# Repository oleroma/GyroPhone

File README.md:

<h1 align="center">
  <picture>
    <source media="(prefers-color-scheme: dark)" srcset="./media/logo_light.svg">
    <source media="(prefers-color-scheme: light)" srcset="./media/logo_dark.svg">
    <!-- The fallback image for older browsers -->
    
  </picture>
  <br>
</h1>

# GyroPhone

GyroPhone turns an Android phone into a game pad, keyboard, mouse and gyro aim for a Windows PC, in the spirit of the [Alpakka](https://github.com/inputlabs/alpakka_firmware) controller. The phone's gyro aims like a mouse. The touchscreen is a laptop-style touchpad plus any buttons and sticks you place on it. A controller, keyboard or mouse attached to the phone can be remapped too. Everything is a mapping you can change: any input can press any output.

It connects two ways:

- **Bluetooth**: the phone is a Bluetooth game pad, keyboard and mouse. Nothing is installed on the PC. Windows sees a DirectInput pad, and input is limited to 30–90 reports a second.
- **Wi-Fi or USB, with the companion**: a small Windows tray app (`GyroPhoneCompanion.exe`) receives up to 1000 updates a second, encrypted. It gives games a virtual **Xbox 360** or **DualShock 4** pad and real keyboard and mouse input, and can draw the phone's motion as overlay windows over the game or for OBS. This is the low-latency way to play.

The reference phone is a OnePlus 15 (Android 16, no root). Android 15 or newer is needed.

The full description of every feature and how it works inside is in the **[spec](docs/spec/README.md)**.

## Setting up

### Phone

Install the APK (`gyrophone-0.1.<build>.apk`). Builds are published as pre-releases on this repo, so [Obtainium](https://github.com/ImranR98/Obtainium) can install and update it (add the repo with pre-releases on). Open GyroPhone and allow the nearby-devices (Bluetooth) and notification permissions. The app opens on the pad.

### Bluetooth (no PC install)

1. On the pad, tap **Connection**, choose **Bluetooth**, and tap **Make discoverable**.
2. On Windows: Settings › Bluetooth & devices › Add device, and pick **GyroPhone**.
3. The phone reconnects to that PC by itself from then on. Set **Report rate** on the same page (60 Hz by default; higher rates queue up and lag on phones that force Bluetooth sniff mode).

### Wi-Fi and USB (companion)

On the PC:

1. Get `GyroPhoneCompanion.exe` from the same pre-release (Windows 10/11 x64), put it in `%LOCALAPPDATA%\Programs\GyroPhone\`, and run it. It is unsigned, so SmartScreen may ask: *More info* › *Run anyway*.
2. For the game pad, install the **ViGEmBus** driver ([github.com/nefarius/ViGEmBus/releases](https://github.com/nefarius/ViGEmBus/releases)). Without it keyboard and mouse still work, and Home in the companion shows how to fix it.
   - Optional: for a **DualSense** pad, run `install.cmd` from the unpacked driver package (`build\GyroPhonePad-driver` after a PC build, or the `GyroPhonePad-driver.zip` of a release), then restart the companion. It's our own user-mode driver, signed with a key made for your PC only; `uninstall.cmd` removes it. Buttons and sticks only for now. See [driver/README.md](driver/README.md).
3. Allow it through the firewall on **Private** networks. The companion never opens Public networks, so if the phone can't connect, set your home Wi-Fi to Private (Home says so when the network is Public and no phone is seen). The Connection page has fix buttons for the firewall and USB rules.
4. On the first run the **Pair new phone** window opens by itself. Later, use *Pair new phone…* in the tray menu.

On the phone:

1. Tap **Connection**, choose **Wi-Fi**, tap **Scan QR code**, and point the camera at the QR code in the PC's pairing window. That's all: both sides trust each other's key, and the phone connects by itself whenever GyroPhone is open (**Connect automatically**, on by default).
2. Or pair with a code: tap the PC under *Found on this network* (or type its address under *Enter PC address*). Check the six-digit code matches on both screens, then tap **Confirm** on the phone and **Allow** on the PC.
3. Keep GyroPhone on screen while playing: Android only grants the low-latency Wi-Fi mode to the app in front. **Link quality** shows the rate, loss and latency.

**USB.** With USB tethering on, the link moves to the cable by itself. With the phone's USB mode set to *No data transfer*, the companion can also use the cable directly (Android asks to open GyroPhone for the accessory; say yes).

**Starting automatically.** In the companion's App page: **Start with Windows**, or **Start when my phone appears** (a tiny watcher starts the companion when the phone looks for this PC).

## The pad

The app is the pad. Along the top is the **capsule row**:

- **+** adds a workspace (Controller, WASD, Keyboard or a blank one, with the touchpad only);
- one capsule per **workspace**: tap to switch, **tap the current one to edit it**;
- **Controller**: what attached devices do;
- **Settings** and **Connection**.

Long-press a capsule and drag it to reorder. The **← / →** corners switch to the previous / next workspace. Press **both together for fullscreen**; press them again, or Back, to leave.

Empty space is the **touchpad**. With the Windows touchpad preset (in the three starting workspaces): one finger moves the cursor, tap clicks, tap-and-drag drags, two fingers scroll, two-finger tap right-clicks, pinch zooms, and three- and four-finger swipes and taps do Task View, show desktop, switch apps, switch desktops and the notification centre. If your phone takes three-finger touches for screenshots, turn that gesture off in the phone's settings.

### Workspaces

A **workspace** is one complete setup: its buttons, sticks and touchpad, their mappings, its gyro and touch settings, its layers, and which **device preset** it uses for attached devices. Workspaces share nothing, so you can duplicate one and change it freely. There are no game profiles and no automatic switching: switch with the capsules or corners.

Settings and mappings pass down: **Defaults** (Settings › Defaults) → **workspace** → **layer** → **button**. A level only stores what it changes. Values a level sets itself are highlighted, and **↺** makes one follow its parent again.

### Edit mode

Tap the current workspace's capsule. A floating menu appears. Drag it by its ⠿ dots to reach what's under it, and drag its right edge to make it wider or narrower. Everything except undo and redo scrolls sideways, so swipe the menu's rows to reach the rest on a narrow (portrait) screen.

- **Tap** a control to select it. Tapping again where controls overlap selects the next one underneath, so taps cycle through a stack.
- **Drag** moves the selected control *from anywhere on the screen*, not only from on top of it, so small controls don't hide under your finger. With nothing selected, a drag moves the control under the finger.
- **Pinch** with two fingers anywhere resizes the selected control. On a rectangle, the pinch locks to one axis if your fingers spread mostly one way (width or height only), and frees the other axis once that one changes too. A **two-finger tap** selects the control under the fingers without opening anything.
- **Long-press** (about half a second) a control to open its mapping editor. Long-press **empty space** for the workspace touchpad's mapping editor. Long-press a **← / → corner** for its size and "Same size for all corners", or a **gyro display** for its settings.
- **Tap empty space** to clear the selection.
- **+ Button**, **+ Empty button** (one that inherits nothing from the touchpad), **+ Stick**, and the **gyro displays** (3D phone, Ratchet ring, Speed graph, Attitude indicator, Bubble disk, 3D shape). Tapping one adds it in the middle; **dragging it out of the menu** drops it where you let go.
- **Configure** opens the selected control's settings; **Map** opens its mapping editor.
- **Select** turns taps into multi-pick (a picked control's whole group comes with it), and a drag then moves everything picked. **Group** / **Ungroup** keep controls together for later moves and pinches. **Snap** puts edges on a grid. 🔒 **Lock layout** stops drags and pinches from moving what was already there; controls you add afterwards stay free until edit mode opens again.
- **Devices** picks the workspace's device preset. **Library** adds a button you saved earlier ("Save to library" in a button's settings); long-press a library button to remove it from the library.
- **↶ / ↷** undo and redo (100 steps; a slider drag counts as one step). **⚙** saves your edits so far and opens the workspace's settings; Back returns to edit mode. **Done** saves; **Cancel** asks before throwing changes away. Your edits survive the app being sent to the background.

Landscape and portrait have separate placements, so edit in the orientation you play in.

## The mapping editor

Every button, stick, the touchpad, the Defaults, and every key of an attached device have the same full-screen mapping editor.

**Layout.** The top half lists the control's **actions** as cards: one per input (for a button: its press, then its touch gestures). Each card holds the outputs it presses as **chips**. The bottom half is the **library** of outputs in tabs: Recent, Presets, Keyboard, Mouse, Gamepad, Gyro, Phone, Touchpad, Layers, Other. A search box finds any output ("W", "LT", "wheel"), and **⌨ Press a key** captures a key from an attached keyboard. Drag the divider to give either half more room.

**Mapping something:**

1. Tap a card to select it, then tap an output in the library to add it there. Tap several outputs to add them all.
2. Or long-press an output and drag it onto any card.
3. Long-press a chip to drag it to another card, or back onto the library to remove it. While dragging, hold near the top or bottom edge to scroll the cards.
4. Reorder cards by their ⠿ handle. **Sort ▾** puts them back in the default order, your own (Custom), or Mapped first.
5. Adding an output a card already presses moves it to the next free **When** and opens its settings, so dropping "Crouch" twice gives you On touch Crouch and Long press Crouch.

**Finger chips** (on buttons and the touchpad) pick which finger count you are mapping: **1–4 fingers**, each with its own taps, holds, swipes, Move X / Move Y and pinch. **Motion** maps the gyro, tilt and shake (on a button: what they do while it is held).

Under a card, a grey line shows its timings ("Tap: at lift before 400 ms · Long press: from 400 ms"). A card's **⚙** opens that input's own settings, such as its own long-press time or a swipe direction's distance and pie.

**Chip settings.** Tap a chip to open its settings:

- **Where** (touch controls): **Touch** (the press), **Inside** (any finger inside the control, wherever it touched down), **Outside** (a finger that touched down on it and slid off).
- **When**: **On touch** (held from touch-down to lift), **Tap**, **Long press**, **Double tap**, **Release**. On swipe directions these read On swipe, Quick swipe, Long hold, Double swipe. Each When is a separate input, so one button can do different things on tap, long press and double tap. A tap only waits for a possible double tap when the double tap does something else.
- **How**: **Held** (for as long as it lasts), **Once** (one short press), **Toggle** (on, then off next time). A Toggle can **also end on** a tap, Let go, a timer, the next input (a sticky Shift), or the same keystroke.
- **Advanced**: start delay, end delay, hold at least, and **Cycle** (the outputs take turns, one per press).
- Analog outputs (mouse motion, sticks) have a **scale**; −1 inverts.

**Inherited mappings** show faded. **✕** clears one (the input then does nothing here), **↺** follows the parent again, **↺ Reset all** follows everything, and **✕ Clear all** clears everything. **↶ Undo** undoes any change.

**Swipe length zones.** A held swipe direction (Swipe ← → ↑ ↓) can do different things the further you swipe. Its row ends in a divider: drag a chip **past that end divider** to make a new zone. Long-press a divider to slide it, and tap the end divider for the last zone's settings (its length and Keep: Only in zone, Only forward, Always). A held direction **latches** (stays on after you lift) when one of its chips is a Toggle that also ends on Tap.

**Layers.** Chips at the top pick **Base** or a layer (**+ Layer**, up to 9). Long-press a layer chip to rename or delete it. A mapping in a layer only works while that layer is in use. Map an input to a **Layer** output (Layers tab) to **switch** to it, **override** Base with it (inputs the layer doesn't map keep their Base mapping), or use it only **while held**. **Layer back** returns to the previous layer. A layer can also have its own settings, for example a lower gyro sensitivity.

**Presets** fill in common setups: **Windows touchpad** for a touch surface, **Gyro mouse** for the gyro (yaw → Move X, pitch → Move Y), and Left stick, Right stick, WASD, Arrow keys and D-pad for sticks.

**⚙ Settings** opens the control's own settings: label, shape and size, layer behaviour, its own touch surface settings, a stick's deadzone and zones, and its own gyro sensitivity while held (for precision aim). For a button it also has **Duplicate**, **Save to library** and **Delete**.

## Gyro aiming

The gyro is mapped like everything else: in the Motion tab, map **yaw / pitch / roll** to mouse Move X / Y, scroll, or a stick axis (or use the Gyro mouse preset). The three starting workspaces already have it.

**Ratchets.** Map a button to **Ratchet** (or Ratchet yaw / pitch / roll) in the Gyro tab. In the workspace's Gyro settings, **Gyro to mouse** sets what it does:

- **Ratchet enables** (default): the gyro does nothing until a ratchet is held.
- **Ratchet disables**: the gyro is always on, and holding a ratchet pauses it so you can re-centre the phone.
- **Gyro off**: the sensor isn't read at all.

**Toggle gyro** swaps the first two until you switch workspace.

**Acceleration curve editor**: tap the graph to add a point (up to 6), drag a point to move it, long-press a point to remove it. Its live line shows how fast you are turning now.

**Tuning** (workspace settings › Gyro): **Sensitivity** in mouse counts per degree (16 by default; per axis, exact, or a 0 to 1 share of the parent's with "Scale parent"); **Game**: pick the game and enter your in-game sensitivity, and the slider shows real-world sensitivity (degrees the camera turns per degree the phone turns; **Measure** helps if your game isn't listed); **Acceleration** curves; **Inertia** (keep gliding after a ratchet); **Gyro space** Local, World or Player (JoyShockMapper's player space). **Calibrate** removes drift: lay the phone still for 2 seconds. Alpakka/JoyShockMapper-style jitter cutoff and smoothing are in Settings › App › Gyro, off by default (raw gyro).

**Gyro poll rate** (Connection page, 1/2/4 kHz, default 4 kHz) is how often the app reads the sensor.

## Controllers and other devices

Attach a game pad, keyboard or mouse to the phone (USB or Bluetooth). The **Controller** capsule shows **device presets** as tabs (**+** adds one, long-press to rename, duplicate or delete). Each preset draws the device: the controller from the front and the back, the keyboard, the mouse, and the phone's volume rocker. Tap any control to open its mapping editor. Every key has the same When / How choices as touch buttons, and a **Motion** tab for what the gyro does while it is held. Stick deadzones, curve and direction pies, and trigger press and full-pull points are in each stick's and trigger's settings. A workspace uses one preset; pick it in edit mode with **Devices**.

**Volume rocker.** While the pad is open, the phone's volume keys turn the **PC's** volume unless you map them to something else (Controller › Phone).

**A controller plugged into the PC** can ratchet the phone's gyro with no extra delay: turn on **Use PC controller for gyro ratchet** (Connection page, Wi-Fi). The ratchet buttons come from the workspace's device preset, and the rest of the controller goes to the game as usual.

## Settings

- **Settings › App**: fullscreen on start, keep the screen on (on by default), **black screen when idle** (the pad goes black after a while without a touch, to save battery while you use a controller; tap to wake, and that tap presses nothing), screen rotation, **send input only while the pad is open** (on by default), corners, touch display (show touches, trails, live mappings), gyro filters, debug tools, and the gyro rate.
- **Settings › Defaults**: the settings and touchpad/motion mappings every workspace uses unless it sets its own.
- **Workspace settings** (⚙ in edit mode): rename, duplicate, delete, copy mappings from another workspace; gyro, tilt and shake, calibration, control opacity, haptics, gesture timings (long press 400 ms and double tap 300 ms by default), and the touchpad. Chips at the top switch between Base and each layer's own settings.
- **Connection**: the link, pairing, report rate, gyro poll rate, PC controller ratchet, and **Stop when idle** (the connection ends after the app has been off screen for 10 minutes by default).

Every settings page has a search box; on Settings it searches App and Defaults at once. Categories fold, and you can **long-press a category's name and drag it** to reorder. Values a workspace or layer sets itself are highlighted with a **↺** to follow the parent again. A ⚙ next to a gyro or touchpad setting opens per-axis or per-direction values.

## The companion

**Tray menu**: status, **Open GyroPhone**, **Pause input**, **Gamepad output** (Xbox 360 / DualShock 4 / DualSense, only with the pad driver / Off), **Overlays**, **Pair new phone…**, **Exit**.

**Main window**: **Home** (problems and their fixes, phone, link, latency and gamepad cards), **Phones** (paired phones, Forget), **Gamepad**, **Overlays**, **Connection** (network, firewall, USB checks), **App** (startup, tray click, logs, Debug window, version).

**Overlays.** Add any number of overlay windows: **Phone** (the phone in 3D with your layout, touches and presses, optionally with controller handles), **3D shape**, **Attitude indicator**, **Bubble disk**. Each has its own size, look, quality, frame rate and turning options (gravity, compass, ease back to straight, Level). Turn on **Edit** to drag and resize them; otherwise the mouse goes through them. For streaming, set the background to **Green** and use an OBS chroma key, with OBS Window Capture. Shortcuts: **Ctrl+Alt+R** Level all, **Ctrl+Alt+O** hide all, **Ctrl+Alt+E** Edit (changeable).

**Updates.** A new build placed next to the running exe as `GyroPhoneCompanion.exe.new` is picked up within seconds: the companion shuts down cleanly, replaces itself and starts again, and the phone reconnects. Settings and pairing in `%APPDATA%\GyroPhone` are kept.

### Things to know

- **Games running as administrator** don't accept injected keyboard and mouse input from a normal app. Home says so: use **Restart as administrator**. The virtual pad isn't affected.
- **Anti-cheat** may ignore injected keyboard and mouse input. Use the game pad output in those games.
- **DualShock 4 and DualSense output carry the phone's gyro and accelerometer**, like a real pad, so games with their own controller gyro (The Finals, Steam Input) can aim with it. It's easy to miss: it moves nothing until you turn on the game's gyro, and then turn the app's gyro mouse off in that workspace, or both move the camera. **Start the game after the phone connects**: games look for gyro only on pads present at launch. Which phone axis drives the pad's yaw, pitch and roll (and Invert) is in workspace settings › Gyro › **PC pad yaw / pitch / roll**; by default the screen is the pad's face (yaw through the screen). In Steam, turn off PlayStation controller support for the game if Steam takes over the pad.
- **Safety.** If the phone goes quiet for 250 ms, or the PC locks or sleeps, everything held is released. If the companion is killed while a key is held, it releases it on its next start.
- **Enhance pointer precision** in Windows changes how gyro moves the desktop cursor. Games that read raw input aren't affected.
- **Bluetooth smooth scrolling** needs the PC to have paired with a current build. After updating from an old one, remove GyroPhone in Windows Bluetooth settings and pair again once.

## Easy to miss

Gestures and actions with no button of their own:

**On the pad**
- **Tap the workspace you're on** (its capsule) to open edit mode. There is no Edit button.
- **Press ← and → together** for fullscreen. In fullscreen they are the only way out besides Back, which is why they never fade below 25 %.
- With **Hide the ← / → corners** on (Settings › App › Corners), **four quick taps anywhere** (or touching where a corner is) bring them back for 3 seconds.
- **Long-press a capsule and drag** to reorder workspaces, Controller, Settings and Connection.
- **On the black screen**, the first tap only wakes the pad; it presses nothing. A controller button mapped to **Black screen** (Other tab) blacks it out at once.
- A **one-finger hold on a button** is its press, but it also counts as a touchpad: with the button's swipes and Move mapped (or inherited from the touchpad), you can press it and aim by sliding in one motion.
- **Show live mappings on buttons** (Settings › App › Touch display) makes a button's label show what it just sent, which helps when learning tap / long press / double tap mappings.

**In the editors**
- See [Edit mode](#edit-mode) and [The mapping editor](#the-mapping-editor) for drag-from-anywhere, two-finger tap, pinch axis lock, long-press on empty space, drag-to-add, swipe zones and layer chips.
- **Controller screen**: long-press a preset's tab to rename it, duplicate it, delete it, or reset its keys' own timings.
- **Inherited values**: anything highlighted is set at this level; **↺** next to it goes back to the parent's value. Faded chips in the mapping editor are inherited; mapping anything on that input replaces them.
- Every confirm-free destructive action (**✕ Clear all**, removing chips) can be undone with **↶ Undo**.

**On the PC**
- **Edit** (tray › Overlays, or Ctrl+Alt+E) makes overlay windows draggable. A **click without a drag** picks a window for its settings, and clicking where windows overlap picks the next one underneath.
- **Level all** (Ctrl+Alt+R) makes the way you hold the phone now show face-on in every overlay.
- **Hide all** (Ctrl+Alt+O) hides every overlay but keeps each one's own Show switch for when you bring them back.
- **Clicking the tray icon** can open the main window or the pairing window: App › Tray icon.
- **Recording on the phone** (debug panel › Record) also saves the PC's side at the same moment.

## Debugging

- **Phone**: Settings › App › Debugging › **Debug tools** shows a panel on the pad with the link, gyro, workspace and layer, what is held, and the newest events. **Record** saves the last 30 s. With the switch off nothing is logged.
- **PC**: App page › **Debug window…** shows the link as the PC sees it, what the game is given, and the PC's events. **Save last 30 s** writes a recording. When the phone records over Wi-Fi or USB, the PC saves its side at the same moment.
- **adb**: `adb shell dumpsys activity service com.oleroma.gyrophone/.service.GamepadService [on|off|record|events N]`. `tools/debug-collect.sh` merges a phone and PC recording into one time-sorted file in `build/debug/`.

## Building

Builds run through the scripts in `.agents/` (see `AGENTS.md` and [Build and release](docs/spec/build-release.md)). On the PC, `bash build/src/.agents/agent-build pc` runs the quick tests, builds only the parts that changed (`gyrophone-0.1.<n>.apk` and/or `GyroPhoneCompanion.exe`), runs the full checks, installs the APK over adb, installs the companion and swaps the key files. You need JDK 17, the Android SDK (API 36) and the .NET 8 SDK on the `PATH` / `JAVA_HOME` / `ANDROID_HOME`. When the PC is offline, the `fallback.yml` workflow does the same on GitHub.

Tests:

```
./gradlew :core:test
dotnet test companion/GyroPhone.Companion.Linux.slnf
```

The companion's protocol and engine tests run on Linux and macOS too. The tray app builds only on Windows:

```
dotnet publish companion/src/GyroPhone.Tray -c Release -r win-x64 --self-contained true -p:PublishSingleFile=true -p:IncludeNativeLibrariesForSelfExtract=true -p:PublishReadyToRun=true -o out
```

OpenCV's native DLLs (for the latency test) land beside the exe in `out`, and the exe needs them there.

## Project layout

| Folder | What it contains |
|---|---|
| `core/` | Plain Kotlin, unit-tested on the JVM: the model (workspaces, mappings, inheritance, device presets), the mapping engine, touch surfaces, gyro math, the HID descriptor, and the wire protocol and crypto. |
| `app/` | The Android app: Bluetooth HID, the Wi-Fi/USB link, gyro and other sensors, controller input, the foreground service, and the Compose UI. |
| `companion/` | The Windows companion in C# (.NET 8): protocol, host engine, ViGEm and SendInput, overlays, tray and main window. Shared test vectors in `core/src/test/resources/protocol/v1/` keep the Kotlin and C# sides in step. |
| `docs/spec/` | The [full spec](docs/spec/README.md). |

What isn't built yet is listed at the end of the [spec overview](docs/spec/README.md).

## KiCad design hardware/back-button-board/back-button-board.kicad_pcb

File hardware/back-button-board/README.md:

# Lean back-button board

A small board behind the phone with 8 back buttons (4 left, 4 right), an RP2040, a USB hub and a
USB-C role controller. The design notes are in the "Lean back-button board: design v1" doc in the
GyroPhone project.

- **Unplugged:** the phone powers the board, and the RP2040 connects straight to the phone. The app
  reads it as a plain USB device.
- **Wired:** the PC powers the board and charges the phone. The hub puts the phone (port 1) and the
  RP2040 (port 2) on the PC, and the companion reads the buttons.

Made with KiCad 7. Newer KiCad versions open it fine, but once it's saved in a newer version, KiCad 7
can't open it again.

## Files

| File | What it is |
| --- | --- |
| `gen_sch.py` | The netlist, written as code. It generates `back-button-board.kicad_sch` |
| `check.py` | Checks that every pin in the schematic sits on the net `gen_sch.py` intends |
| `gen_pcb.py` | Builds the board file from the schematic, or moves the buttons and sockets on it |
| `board-settings.json` | Board size, button positions and socket edges |
| `sexp.py` | Small helper for reading and writing KiCad files |

The schematic labels every pin with its net name and draws no wires. That keeps it generated: edit
`gen_sch.py`, never the `.kicad_sch` file.

## Changing the button positions

Edit `board-settings.json`:

- `first_from_top_corner_mm`: where the first button on each side sits, measured from the top
  left corner (the right side mirrors it).
- `step_mm`: how far each next button moves toward the centre (`x`) and down (`y`).
- `rotation_deg`: the rotation of all buttons, so their pads can point wherever routing is easiest.

Then run `gen_pcb.py` with KiCad's Python (the one that can `import pcbnew`). Without `--new`, it
moves only the buttons and sockets and keeps everything else, so after a move only the button traces
need routing again. `--new` rebuilds the board from scratch and throws away any routing.

```
python3 gen_sch.py && python3 check.py     # after changing the netlist
python3 gen_pcb.py                          # after changing board-settings.json
python3 gen_pcb.py --new                    # start the board over
```

On Windows, run the scripts from the KiCad command prompt so `kicad-cli` and `pcbnew` are found.

## Status

- Schematic: complete first draft. KiCad 7's command line has no ERC, so it's checked with
  `check.py` and still needs a run of ERC in the KiCad window.
- Board: 4 layers, 150 × 70 mm placeholder outline. The buttons and sockets come from the
  settings. Everything else is piled in the middle for hand placement. Nothing is routed yet.

## Parts that differ from the design doc

These are equivalents that have symbols and footprints in KiCad's own libraries:

- **Hub:** CH334R (QSOP-16) instead of CH334P, from the same family with the same pins for our use.
  It's powered only from the PC socket, so it draws nothing when unplugged.
- **USB switches:** TS3USB30E instead of TS3USB221. Both are 1:2 high-speed USB switches.
- **Power switches:** AP22814A (3 A, active-high enable). Both switches block reverse current when
  off: PC socket to rail, and rail to phone socket.
- **Hub reset:** through a BAT54 diode from GPIO13, as the CH334 datasheet recommends. This keeps
  its charging-port pin from being forced on at power-up.

## RP2040 pins

| GPIO | Net |
| --- | --- |
| 0–3 | BTN_L1–L4 |
| 4–7 | BTN_R1–R4 |
| 13 | HUB_RST_N (through D2) |
| 14 | MUX_SEL: low = phone straight to the RP2040, high = both through the hub |
| 16 | FUSB_INT_N |
| 18 | PHONE_PWR_EN |
| 19 | PHONE_PWR_FLG_N |
| 20, 21 | I2C SDA, SCL to the FUSB302 |
| 22 | PC_VBUS_DET (PC power, halved) |
| 26, 27 | PC_CC1, PC_CC2 (ADC: the current the PC offers) |

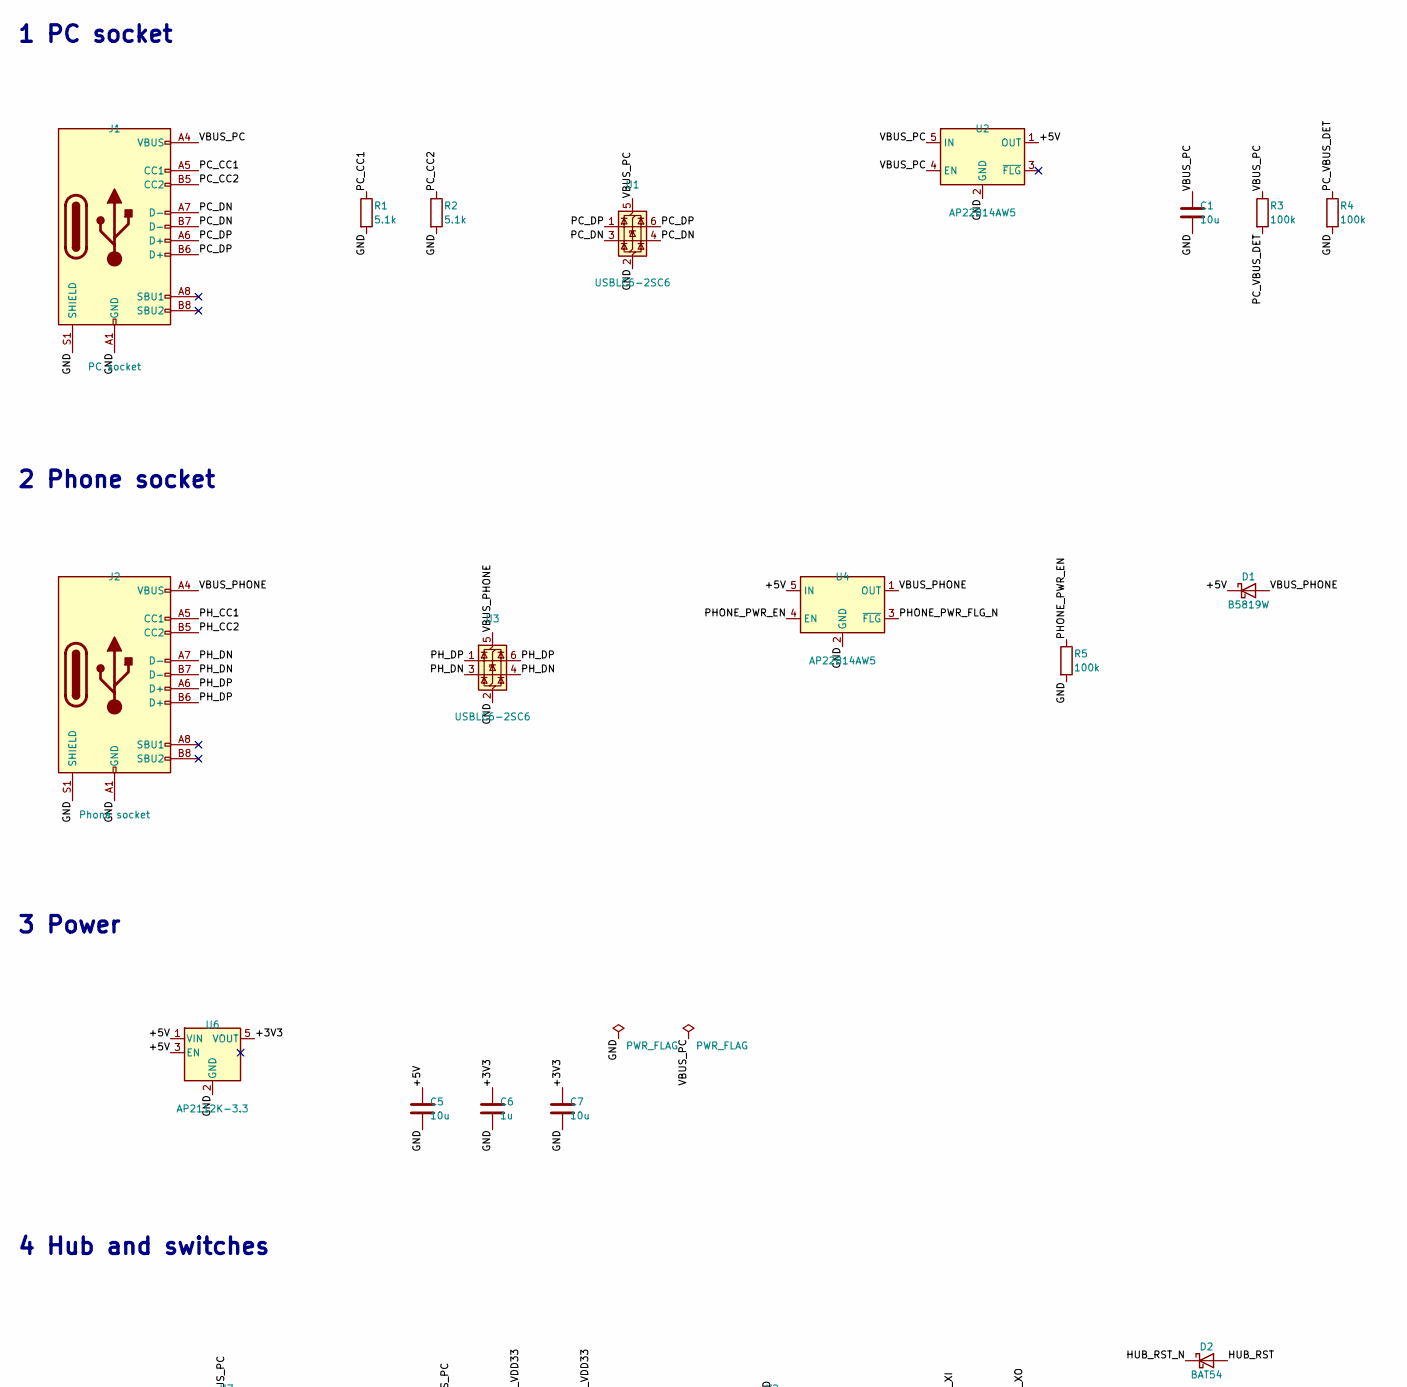
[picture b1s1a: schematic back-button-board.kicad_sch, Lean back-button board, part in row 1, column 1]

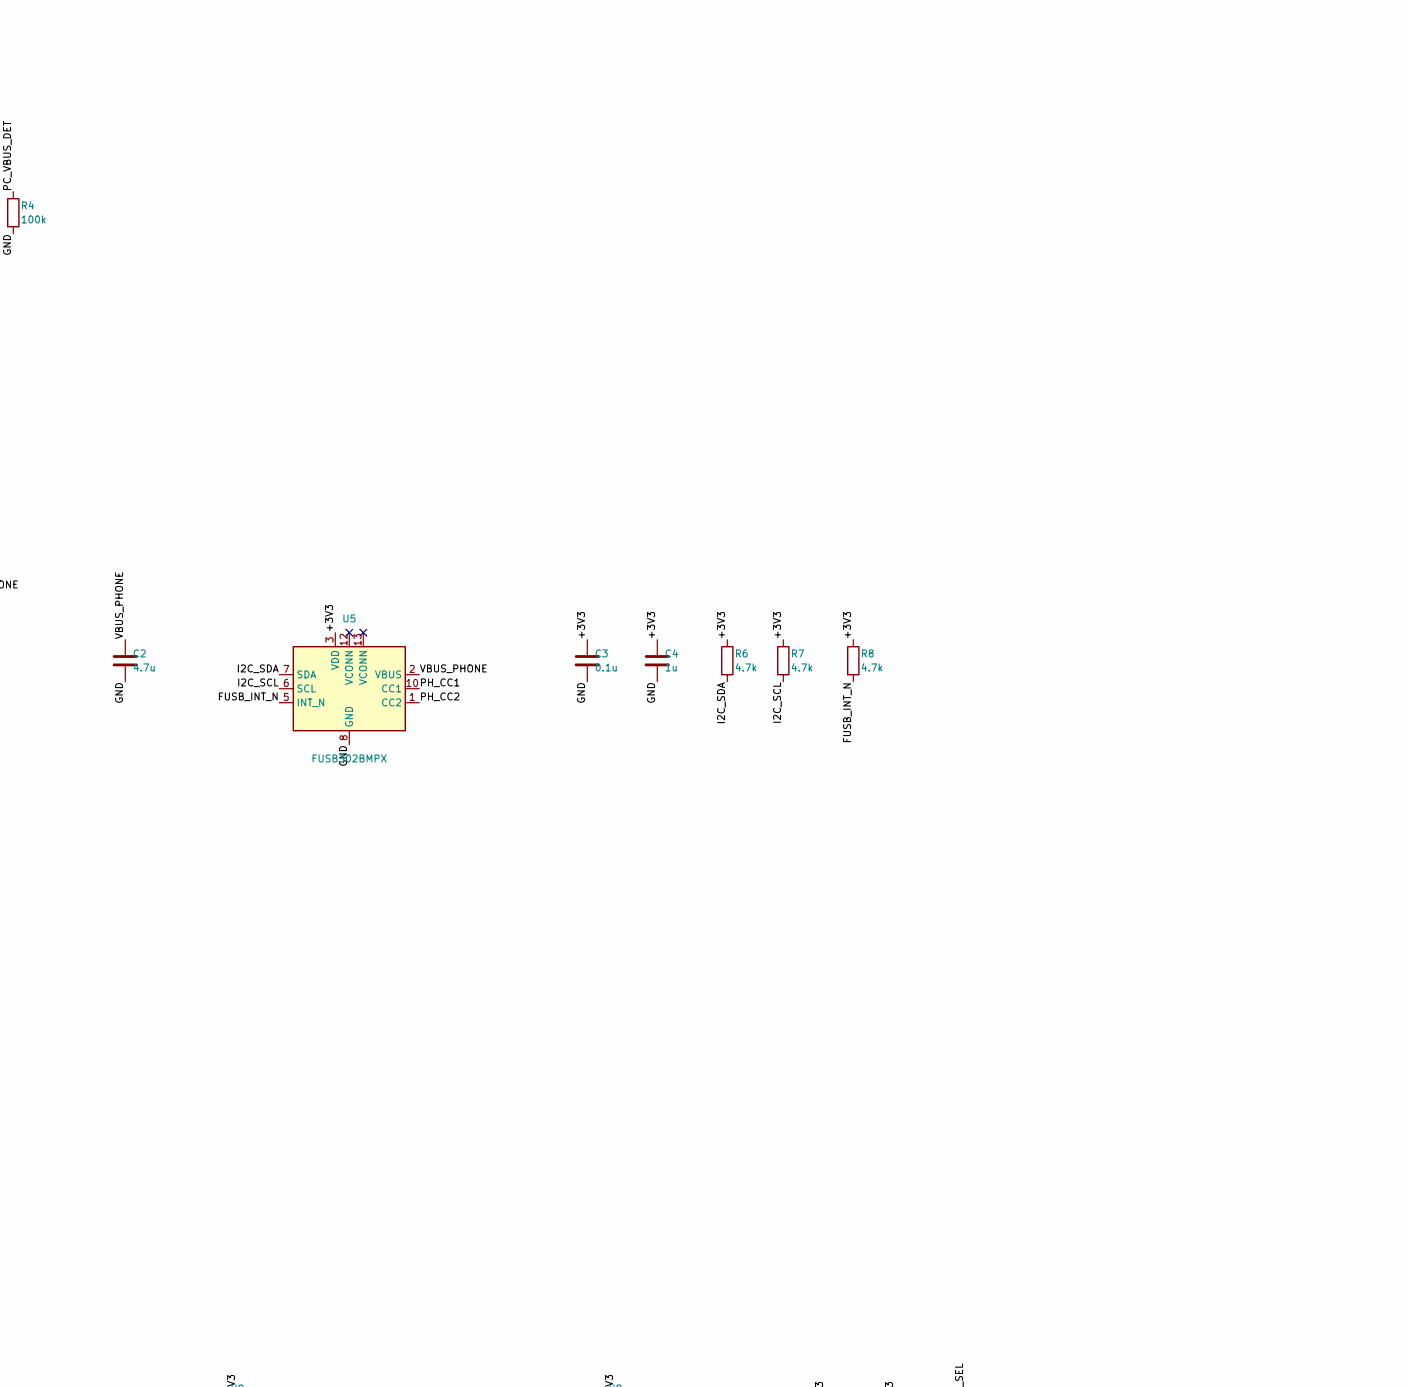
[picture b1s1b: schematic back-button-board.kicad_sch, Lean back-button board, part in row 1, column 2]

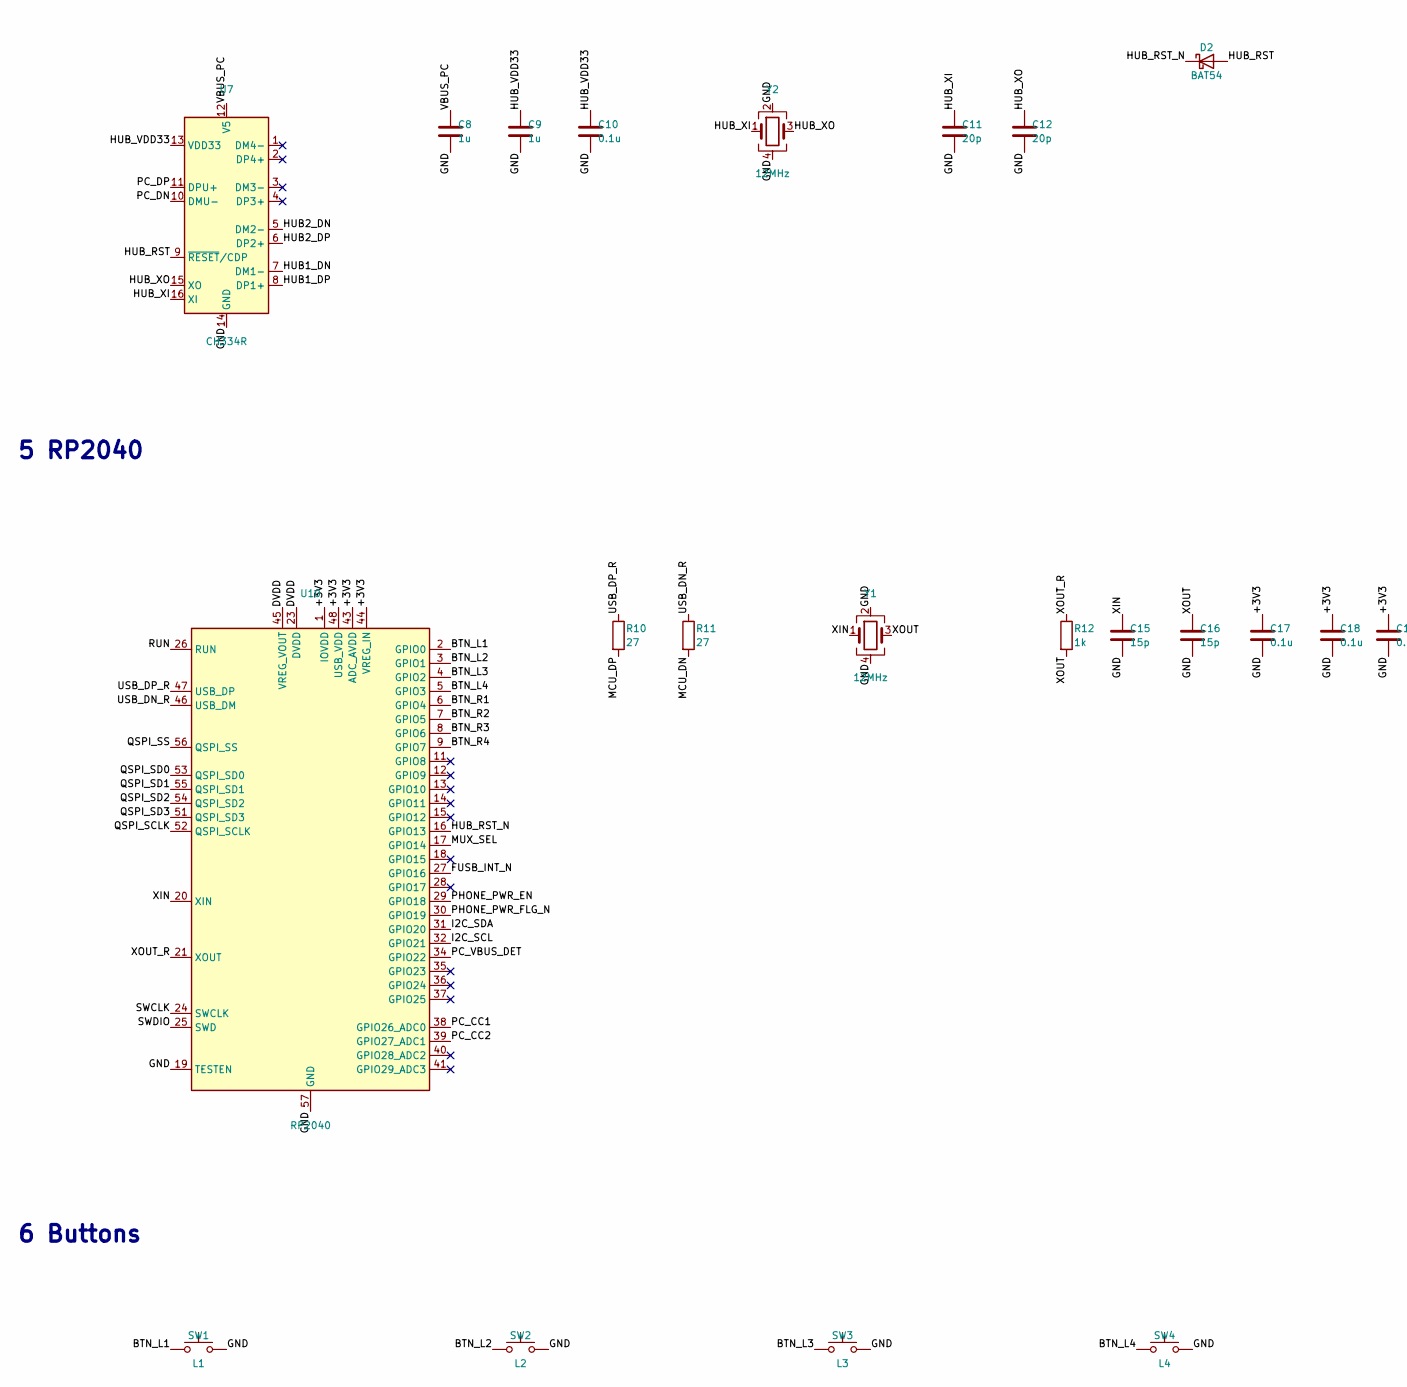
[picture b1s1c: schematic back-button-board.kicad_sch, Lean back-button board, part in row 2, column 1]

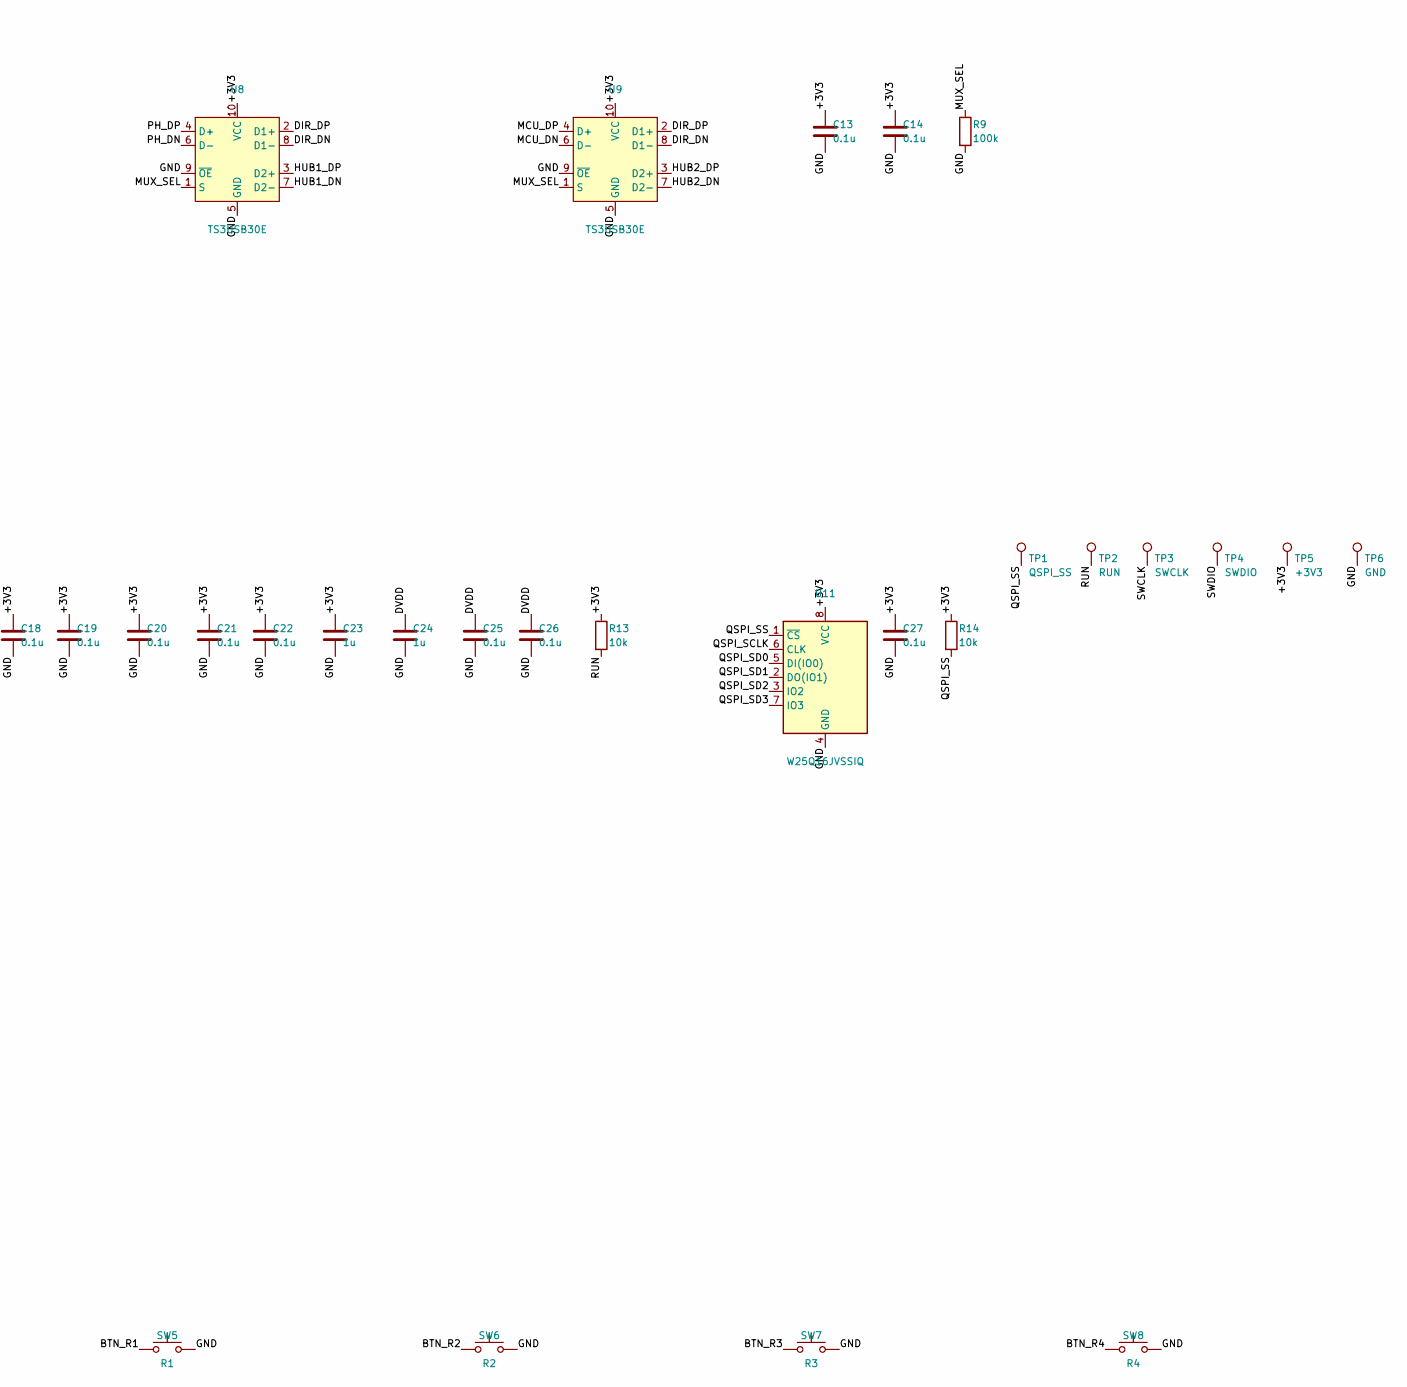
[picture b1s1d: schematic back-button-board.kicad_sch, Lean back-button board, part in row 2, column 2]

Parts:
C1, C5, C7: 10u; C_0603_1608Metric
C2: 4.7u; C_0603_1608Metric
C3, C10, C13, C14, C17, C18, C19, C20, C21, C22, C25, C26, C27: 0.1u; C_0402_1005Metric
C4, C6, C8, C9, C23, C24: 1u; C_0402_1005Metric
C11, C12: 20p; C_0402_1005Metric
C15, C16: 15p; C_0402_1005Metric
D1: B5819W; D_SOD-123
D2: BAT54; SOT-23
J1: PC socket; USB_C_Receptacle_HRO_TYPE-C-31-M-12
J2: Phone socket; USB_C_Receptacle_HRO_TYPE-C-31-M-12
R1, R2: 5.1k; R_0402_1005Metric
R3, R4, R5, R9: 100k; R_0402_1005Metric
R6, R7, R8: 4.7k; R_0402_1005Metric
R10, R11: 27; R_0402_1005Metric
R12: 1k; R_0402_1005Metric
R13, R14: 10k; R_0402_1005Metric
SW1: L1; SW_SPST_SKQG_WithoutStem
SW2: L2; SW_SPST_SKQG_WithoutStem
SW3: L3; SW_SPST_SKQG_WithoutStem
SW4: L4; SW_SPST_SKQG_WithoutStem
SW5: R1; SW_SPST_SKQG_WithoutStem
SW6: R2; SW_SPST_SKQG_WithoutStem
SW7: R3; SW_SPST_SKQG_WithoutStem
SW8: R4; SW_SPST_SKQG_WithoutStem
TP1: QSPI_SS; TestPoint_Pad_D1.0mm
TP2: RUN; TestPoint_Pad_D1.0mm
TP3: SWCLK; TestPoint_Pad_D1.0mm
TP4: SWDIO; TestPoint_Pad_D1.0mm
TP5: +3V3; TestPoint_Pad_D1.0mm
TP6: GND; TestPoint_Pad_D1.0mm
U1, U3: USBLC6-2SC6; SOT-23-6
U2, U4: AP22814AW5; SOT-23-5
U5: FUSB302BMPX; WQFN-14-1EP_2.5x2.5mm_P0.5mm_EP1.45x1.45mm
U6: AP2112K-3.3; SOT-23-5
U7: CH334R; QSOP-16_3.9x4.9mm_P0.635mm
U8, U9: TS3USB30E; VSSOP-10_3x3mm_P0.5mm
U10: RP2040; QFN-56-1EP_7x7mm_P0.4mm_EP3.2x3.2mm
U11: W25Q16JVSSIQ; SOIC-8_5.23x5.23mm_P1.27mm
Y1, Y2: 12MHz; Crystal_SMD_3225-4Pin_3.2x2.5mm

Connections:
+3V3: C3.1, C4.1, C6.1, C7.1, C13.1, C14.1, C17.1, C18.1, C19.1, C20.1, C21.1, C22.1, C23.1, C27.1, R6.1, R7.1, R8.1, R13.1, R14.1, TP5.1, U5.3 (VDD), U5.4 (VDD), U6.5 (VOUT), U8.10 (VCC), U9.10 (VCC), U10.1 (IOVDD), U10.10 (IOVDD), U10.22 (IOVDD), U10.33 (IOVDD), U10.42 (IOVDD), U10.43 (ADC_AVDD), U10.44 (VREG_IN), U10.48 (USB_VDD), U10.49 (IOVDD), U11.8 (VCC)
+5V: C5.1, D1.1 (K), U2.1 (OUT), U4.5 (IN), U6.1 (VIN), U6.3 (EN)
BTN_L1: SW1.1, U10.2 (GPIO0)
BTN_L2: SW2.1, U10.3 (GPIO1)
BTN_L3: SW3.1, U10.4 (GPIO2)
BTN_L4: SW4.1, U10.5 (GPIO3)
BTN_R1: SW5.1, U10.6 (GPIO4)
BTN_R2: SW6.1, U10.7 (GPIO5)
BTN_R3: SW7.1, U10.8 (GPIO6)
BTN_R4: SW8.1, U10.9 (GPIO7)
DIR_DN: U8.8 (D1-), U9.8 (D1-)
DIR_DP: U8.2 (D1+), U9.2 (D1+)
DVDD: C24.1, C25.1, C26.1, U10.23 (DVDD), U10.45 (VREG_VOUT), U10.50 (DVDD)
FUSB_INT_N: R8.2, U5.5 (INT_N), U10.27 (GPIO16)
GND: C1.2, C2.2, C3.2, C4.2, C5.2, C6.2, C7.2, C8.2, C9.2, C10.2, C11.2, C12.2, C13.2, C14.2, C15.2, C16.2, C17.2, C18.2, C19.2, C20.2, C21.2, C22.2, C23.2, C24.2, C25.2, C26.2, C27.2, J1.A1 (GND), J1.A12 (GND), J1.B1 (GND), J1.B12 (GND), J1.S1 (SHIELD), J2.A1 (GND), J2.A12 (GND), J2.B1 (GND), J2.B12 (GND), J2.S1 (SHIELD), R1.2, R2.2, R4.2, R5.2, R9.2, SW1.2, SW2.2, SW3.2, SW4.2, SW5.2, SW6.2, SW7.2, SW8.2, TP6.1, U1.2 (GND), U2.2 (GND), U3.2 (GND), U4.2 (GND), U5.8 (GND), U5.9 (GND), U5.15 (GND), U6.2 (GND), U7.14 (GND), U8.5 (GND), U8.9 (~OE), U9.5 (GND), U9.9 (~OE), U10.19 (TESTEN), U10.57 (GND), U11.4 (GND), Y1.2, Y1.4, Y2.2, Y2.4
HUB1_DN: U7.7 (DM1-), U8.7 (D2-)
HUB1_DP: U7.8 (DP1+), U8.3 (D2+)
HUB2_DN: U7.5 (DM2-), U9.7 (D2-)
HUB2_DP: U7.6 (DP2+), U9.3 (D2+)
HUB_RST: D2.2 (A), U7.9 (~RESET/CDP)
HUB_RST_N: D2.1 (K), U10.16 (GPIO13)
HUB_VDD33: C9.1, C10.1, U7.13 (VDD33)
HUB_XI: C11.1, U7.16 (XI), Y2.1
HUB_XO: C12.1, U7.15 (XO), Y2.3
I2C_SCL: R7.2, U5.6 (SCL), U10.32 (GPIO21)
I2C_SDA: R6.2, U5.7 (SDA), U10.31 (GPIO20)
MCU_DN: R11.2, U9.6 (D-)
MCU_DP: R10.2, U9.4 (D+)
MUX_SEL: R9.1, U8.1 (S), U9.1 (S), U10.17 (GPIO14)
PC_CC1: J1.A5 (CC1), R1.1, U10.38 (GPIO26_ADC0)
PC_CC2: J1.B5 (CC2), R2.1, U10.39 (GPIO27_ADC1)
PC_DN: J1.A7 (D-), J1.B7 (D-), U1.3 (I/O2), U1.4 (I/O2), U7.10 (DMU-)
PC_DP: J1.A6 (D+), J1.B6 (D+), U1.1 (I/O1), U1.6 (I/O1), U7.11 (DPU+)
PC_VBUS_DET: R3.2, R4.1, U10.34 (GPIO22)
PHONE_PWR_EN: R5.1, U4.4 (EN), U10.29 (GPIO18)
PHONE_PWR_FLG_N: U4.3 (~FLG), U10.30 (GPIO19)
PH_CC1: J2.A5 (CC1), U5.10 (CC1), U5.11 (CC1)
PH_CC2: J2.B5 (CC2), U5.1 (CC2), U5.14 (CC2)
PH_DN: J2.A7 (D-), J2.B7 (D-), U3.3 (I/O2), U3.4 (I/O2), U8.6 (D-)
PH_DP: J2.A6 (D+), J2.B6 (D+), U3.1 (I/O1), U3.6 (I/O1), U8.4 (D+)
QSPI_SCLK: U10.52 (QSPI_SCLK), U11.6 (CLK)
QSPI_SD0: U10.53 (QSPI_SD0), U11.5 (DI(IO0))
QSPI_SD1: U10.55 (QSPI_SD1), U11.2 (DO(IO1))
QSPI_SD2: U10.54 (QSPI_SD2), U11.3 (IO2)
QSPI_SD3: U10.51 (QSPI_SD3), U11.7 (IO3)
QSPI_SS: R14.2, TP1.1, U10.56 (QSPI_SS), U11.1 (~CS)
RUN: R13.2, TP2.1, U10.26 (RUN)
SWCLK: TP3.1, U10.24 (SWCLK)
SWDIO: TP4.1, U10.25 (SWD)
USB_DN_R: R11.1, U10.46 (USB_DM)
USB_DP_R: R10.1, U10.47 (USB_DP)
VBUS_PC: C1.1, C8.1, J1.A4 (VBUS), J1.A9 (VBUS), J1.B4 (VBUS), J1.B9 (VBUS), R3.1, U1.5 (VBUS), U2.4 (EN), U2.5 (IN), U7.12 (V5)
VBUS_PHONE: C2.1, D1.2 (A), J2.A4 (VBUS), J2.A9 (VBUS), J2.B4 (VBUS), J2.B9 (VBUS), U3.5 (VBUS), U4.1 (OUT), U5.2 (VBUS)
XIN: C15.1, U10.20 (XIN), Y1.1
XOUT: C16.1, R12.2, Y1.3
XOUT_R: R12.1, U10.21 (XOUT)

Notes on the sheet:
1 PC socket
2 Phone socket
3 Power
4 Hub and switches
5 RP2040
6 Buttons

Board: 4 copper layers, 72 parts (0 on the bottom side), 56 nets, no tracks yet.

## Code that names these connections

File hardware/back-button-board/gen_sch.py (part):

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
# --- RP2040 and flash
g = '5 RP2040'
gpio = {0: 'BTN_L1', 1: 'BTN_L2', 2: 'BTN_L3', 3: 'BTN_L4', 4: 'BTN_R1', 5: 'BTN_R2', 6: 'BTN_R3', 7: 'BTN_R4',
        13: 'HUB_RST_N', 14: 'MUX_SEL', 16: 'FUSB_INT_N', 18: 'PHONE_PWR_EN', 19: 'PHONE_PWR_FLG_N',
        20: 'I2C_SDA', 21: 'I2C_SCL', 22: 'PC_VBUS_DET'}
mcu = {'1': '+3V3', '10': '+3V3', '22': '+3V3', '33': '+3V3', '42': '+3V3', '49': '+3V3',
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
